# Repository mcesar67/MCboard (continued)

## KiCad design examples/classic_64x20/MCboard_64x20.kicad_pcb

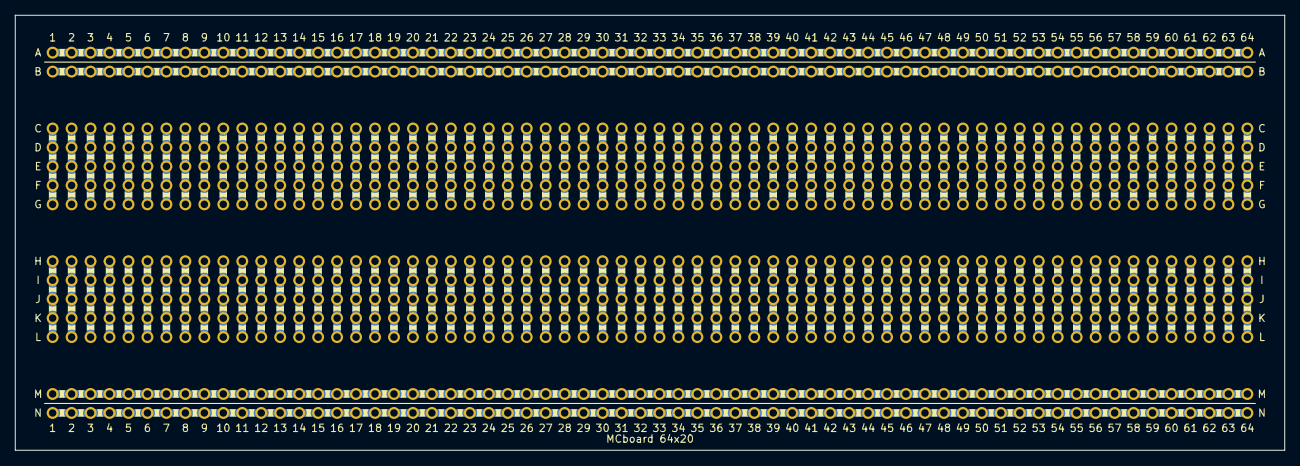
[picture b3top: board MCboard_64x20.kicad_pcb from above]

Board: 2 copper layers, 170.0 x 58.3 mm, 896 parts (0 on the bottom side), 132 nets.

Parts:
PBH1, PBH2, PBH3, PBH4, PBH5, PBH6, PBH7, PBH8, PBH9, PBH10, PBH11, PBH12, PBH13, PBH14, PBH15, PBH16, PBH17, PBH18, PBH19, PBH20, PBH21, PBH22, PBH23, PBH24, PBH25, PBH26, PBH27, PBH28, PBH29, PBH30, PBH31, PBH32, PBH33, PBH34, PBH35, PBH36, PBH37, PBH38, PBH39, PBH40, PBH41, PBH42, PBH43, PBH44, PBH45, PBH46, PBH47, PBH48, PBH49, PBH50, PBH51, PBH52, PBH53, PBH54, PBH55, PBH56, PBH57, PBH58, PBH59, PBH60, PBH61, PBH62, PBH63, PBH64, PBH65, PBH66, PBH67, PBH68, PBH69, PBH70, PBH71, PBH72, PBH73, PBH74, PBH75, PBH76, PBH77, PBH78, PBH79, PBH80, PBH81, PBH82, PBH83, PBH84, PBH85, PBH86, PBH87, PBH88, PBH89, PBH90, PBH91, PBH92, PBH93, PBH94, PBH95, PBH96, PBH97, PBH98, PBH99, PBH100, PBH101, PBH102, PBH103, PBH104, PBH105, PBH106, PBH107, PBH108, PBH109, PBH110, PBH111, PBH112, PBH113, PBH114, PBH115, PBH116, PBH117, PBH118, PBH119, PBH120, PBH121, PBH122, PBH123, PBH124, PBH125, PBH126, PBH127, PBH128, PBH129, PBH130, PBH131, PBH132, PBH133, PBH134, PBH135, PBH136, PBH137, PBH138, PBH139, PBH140, PBH141, PBH142, PBH143, PBH144, PBH145, PBH146, PBH147, PBH148, PBH149, PBH150, PBH151, PBH152, PBH153, PBH154, PBH155, PBH156, PBH157, PBH158, PBH159, PBH160, PBH161, PBH162, PBH163, PBH164, PBH165, PBH166, PBH167, PBH168, PBH169, PBH170, PBH171, PBH172, PBH173, PBH174, PBH175, PBH176, PBH177, PBH178, PBH179, PBH180, PBH181, PBH182, PBH183, PBH184, PBH185, PBH186, PBH187, PBH188, PBH189, PBH190, PBH191, PBH192, PBH193, PBH194, PBH195, PBH196, PBH197, PBH198, PBH199, PBH200, PBH201, PBH202, PBH203, PBH204, PBH205, PBH206, PBH207, PBH208, PBH209, PBH210, PBH211, PBH212, PBH213, PBH214, PBH215, PBH216, PBH217, PBH218, PBH219, PBH220, PBH221, PBH222, PBH223, PBH224, PBH225, PBH226, PBH227, PBH228, PBH229, PBH230, PBH231, PBH232, PBH233, PBH234, PBH235, PBH236, PBH237, PBH238, PBH239, PBH240, PBH241, PBH242, PBH243, PBH244, PBH245, PBH246, PBH247, PBH248, PBH249, PBH250, PBH251, PBH252, PBH253, PBH254, PBH255, PBH256, PBH257, PBH258, PBH259, PBH260, PBH261, PBH262, PBH263, PBH264, PBH265, PBH266, PBH267, PBH268, PBH269, PBH270, PBH271, PBH272, PBH273, PBH274, PBH275, PBH276, PBH277, PBH278, PBH279, PBH280, PBH281, PBH282, PBH283, PBH284, PBH285, PBH286, PBH287, PBH288, PBH289, PBH290, PBH291, PBH292, PBH293, PBH294, PBH295, PBH296, PBH297, PBH298, PBH299, PBH300, PBH301, PBH302, PBH303, PBH304, PBH305, PBH306, PBH307, PBH308, PBH309, PBH310, PBH311, PBH312, PBH313, PBH314, PBH315, PBH316, PBH317, PBH318, PBH319, PBH320, PBH321, PBH322, PBH323, PBH324, PBH325, PBH326, PBH327, PBH328, PBH329, PBH330, PBH331, PBH332, PBH333, PBH334, PBH335, PBH336, PBH337, PBH338, PBH339, PBH340, PBH341, PBH342, PBH343, PBH344, PBH345, PBH346, PBH347, PBH348, PBH349, PBH350, PBH351, PBH352, PBH353, PBH354, PBH355, PBH356, PBH357, PBH358, PBH359, PBH360, PBH361, PBH362, PBH363, PBH364, PBH365, PBH366, PBH367, PBH368, PBH369, PBH370, PBH371, PBH372, PBH373, PBH374, PBH375, PBH376, PBH377, PBH378, PBH379, PBH380, PBH381, PBH382, PBH383, PBH384, PBH385, PBH386, PBH387, PBH388, PBH389, PBH390, PBH391, PBH392, PBH393, PBH394, PBH395, PBH396, PBH397, PBH398, PBH399, PBH400, PBH401, PBH402, PBH403, PBH404, PBH405, PBH406, PBH407, PBH408, PBH409, PBH410, PBH411, PBH412, PBH413, PBH414, PBH415, PBH416, PBH417, PBH418, PBH419, PBH420, PBH421, PBH422, PBH423, PBH424, PBH425, PBH426, PBH427, PBH428, PBH429, PBH430, PBH431, PBH432, PBH433, PBH434, PBH435, PBH436, PBH437, PBH438, PBH439, PBH440, PBH441, PBH442, PBH443, PBH444, PBH445, PBH446, PBH447, PBH448, PBH449, PBH450, PBH451, PBH452, PBH453, PBH454, PBH455, PBH456, PBH457, PBH458, PBH459, PBH460, PBH461, PBH462, PBH463, PBH464, PBH465, PBH466, PBH467, PBH468, PBH469, PBH470, PBH471, PBH472, PBH473, PBH474, PBH475, PBH476, PBH477, PBH478, PBH479, PBH480, PBH481, PBH482, PBH483, PBH484, PBH485, PBH486, PBH487, PBH488, PBH489, PBH490, PBH491, PBH492, PBH493, PBH494, PBH495, PBH496, PBH497, PBH498, PBH499, PBH500, PBH501, PBH502, PBH503, PBH504, PBH505, PBH506, PBH507, PBH508, PBH509, PBH510, PBH511, PBH512, PBH513, PBH514, PBH515, PBH516, PBH517, PBH518, PBH519, PBH520, PBH521, PBH522, PBH523, PBH524, PBH525, PBH526, PBH527, PBH528, PBH529, PBH530, PBH531, PBH532, PBH533, PBH534, PBH535, PBH536, PBH537, PBH538, PBH539, PBH540, PBH541, PBH542, PBH543, PBH544, PBH545, PBH546, PBH547, PBH548, PBH549, PBH550, PBH551, PBH552, PBH553, PBH554, PBH555, PBH556, PBH557, PBH558, PBH559, PBH560, PBH561, PBH562, PBH563, PBH564, PBH565, PBH566, PBH567, PBH568, PBH569, PBH570, PBH571, PBH572, PBH573, PBH574, PBH575, PBH576, PBH577, PBH578, PBH579, PBH580, PBH581, PBH582, PBH583, PBH584, PBH585, PBH586, PBH587, PBH588, PBH589, PBH590, PBH591, PBH592, PBH593, PBH594, PBH595, PBH596, PBH597, PBH598, PBH599, PBH600, PBH601, PBH602, PBH603, PBH604, PBH605, PBH606, PBH607, PBH608, PBH609, PBH610, PBH611, PBH612, PBH613, PBH614, PBH615, PBH616, PBH617, PBH618, PBH619, PBH620, PBH621, PBH622, PBH623, PBH624, PBH625, PBH626, PBH627, PBH628, PBH629, PBH630, PBH631, PBH632, PBH633, PBH634, PBH635, PBH636, PBH637, PBH638, PBH639, PBH640, PBH641, PBH642, PBH643, PBH644, PBH645, PBH646, PBH647, PBH648, PBH649, PBH650, PBH651, PBH652, PBH653, PBH654, PBH655, PBH656, PBH657, PBH658, PBH659, PBH660, PBH661, PBH662, PBH663, PBH664, PBH665, PBH666, PBH667, PBH668, PBH669, PBH670, PBH671, PBH672, PBH673, PBH674, PBH675, PBH676, PBH677, PBH678, PBH679, PBH680, PBH681, PBH682, PBH683, PBH684, PBH685, PBH686, PBH687, PBH688, PBH689, PBH690, PBH691, PBH692, PBH693, PBH694, PBH695, PBH696, PBH697, PBH698, PBH699, PBH700, PBH701, PBH702, PBH703, PBH704, PBH705, PBH706, PBH707, PBH708, PBH709, PBH710, PBH711, PBH712, PBH713, PBH714, PBH715, PBH716, PBH717, PBH718, PBH719, PBH720, PBH721, PBH722, PBH723, PBH724, PBH725, PBH726, PBH727, PBH728, PBH729, PBH730, PBH731, PBH732, PBH733, PBH734, PBH735, PBH736, PBH737, PBH738, PBH739, PBH740, PBH741, PBH742, PBH743, PBH744, PBH745, PBH746, PBH747, PBH748, PBH749, PBH750, PBH751, PBH752, PBH753, PBH754, PBH755, PBH756, PBH757, PBH758, PBH759, PBH760, PBH761, PBH762, PBH763, PBH764, PBH765, PBH766, PBH767, PBH768, PBH769, PBH770, PBH771, PBH772, PBH773, PBH774, PBH775, PBH776, PBH777, PBH778, PBH779, PBH780, PBH781, PBH782, PBH783, PBH784, PBH785, PBH786, PBH787, PBH788, PBH789, PBH790, PBH791, PBH792, PBH793, PBH794, PBH795, PBH796, PBH797, PBH798, PBH799, PBH800, PBH801, PBH802, PBH803, PBH804, PBH805, PBH806, PBH807, PBH808, PBH809, PBH810, PBH811, PBH812, PBH813, PBH814, PBH815, PBH816, PBH817, PBH818, PBH819, PBH820, PBH821, PBH822, PBH823, PBH824, PBH825, PBH826, PBH827, PBH828, PBH829, PBH830, PBH831, PBH832, PBH833, PBH834, PBH835, PBH836, PBH837, PBH838, PBH839, PBH840, PBH841, PBH842, PBH843, PBH844, PBH845, PBH846, PBH847, PBH848, PBH849, PBH850, PBH851, PBH852, PBH853, PBH854, PBH855, PBH856, PBH857, PBH858, PBH859, PBH860, PBH861, PBH862, PBH863, PBH864, PBH865, PBH866, PBH867, PBH868, PBH869, PBH870, PBH871, PBH872, PBH873, PBH874, PBH875, PBH876, PBH877, PBH878, PBH879, PBH880, PBH881, PBH882, PBH883, PBH884, PBH885, PBH886, PBH887, PBH888, PBH889, PBH890, PBH891, PBH892, PBH893, PBH894, PBH895, PBH896: hole; Hole

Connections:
BUS_R1: PBH1.1, PBH15.1, PBH29.1, PBH43.1, PBH57.1, PBH71.1, PBH85.1, PBH99.1, PBH113.1, PBH127.1, PBH141.1, PBH155.1, PBH169.1, PBH183.1, PBH197.1, PBH211.1, PBH225.1, PBH239.1, PBH253.1, PBH267.1, PBH281.1, PBH295.1, PBH309.1, PBH323.1, PBH337.1, PBH351.1, PBH365.1, PBH379.1, PBH393.1, PBH407.1, PBH421.1, PBH435.1, PBH449.1, PBH463.1, PBH477.1, PBH491.1, PBH505.1, PBH519.1, PBH533.1, PBH547.1, PBH561.1, PBH575.1, PBH589.1, PBH603.1, PBH617.1, PBH631.1, PBH645.1, PBH659.1, PBH673.1, PBH687.1, PBH701.1, PBH715.1, PBH729.1, PBH743.1, PBH757.1, PBH771.1, PBH785.1, PBH799.1, PBH813.1, PBH827.1, PBH841.1, PBH855.1, PBH869.1, PBH883.1
BUS_R2: PBH2.1, PBH16.1, PBH30.1, PBH44.1, PBH58.1, PBH72.1, PBH86.1, PBH100.1, PBH114.1, PBH128.1, PBH142.1, PBH156.1, PBH170.1, PBH184.1, PBH198.1, PBH212.1, PBH226.1, PBH240.1, PBH254.1, PBH268.1, PBH282.1, PBH296.1, PBH310.1, PBH324.1, PBH338.1, PBH352.1, PBH366.1, PBH380.1, PBH394.1, PBH408.1, PBH422.1, PBH436.1, PBH450.1, PBH464.1, PBH478.1, PBH492.1, PBH506.1, PBH520.1, PBH534.1, PBH548.1, PBH562.1, PBH576.1, PBH590.1, PBH604.1, PBH618.1, PBH632.1, PBH646.1, PBH660.1, PBH674.1, PBH688.1, PBH702.1, PBH716.1, PBH730.1, PBH744.1, PBH758.1, PBH772.1, PBH786.1, PBH800.1, PBH814.1, PBH828.1, PBH842.1, PBH856.1, PBH870.1, PBH884.1
BUS_R13: PBH13.1, PBH27.1, PBH41.1, PBH55.1, PBH69.1, PBH83.1, PBH97.1, PBH111.1, PBH125.1, PBH139.1, PBH153.1, PBH167.1, PBH181.1, PBH195.1, PBH209.1, PBH223.1, PBH237.1, PBH251.1, PBH265.1, PBH279.1, PBH293.1, PBH307.1, PBH321.1, PBH335.1, PBH349.1, PBH363.1, PBH377.1, PBH391.1, PBH405.1, PBH419.1, PBH433.1, PBH447.1, PBH461.1, PBH475.1, PBH489.1, PBH503.1, PBH517.1, PBH531.1, PBH545.1, PBH559.1, PBH573.1, PBH587.1, PBH601.1, PBH615.1, PBH629.1, PBH643.1, PBH657.1, PBH671.1, PBH685.1, PBH699.1, PBH713.1, PBH727.1, PBH741.1, PBH755.1, PBH769.1, PBH783.1, PBH797.1, PBH811.1, PBH825.1, PBH839.1, PBH853.1, PBH867.1, PBH881.1, PBH895.1
BUS_R14: PBH14.1, PBH28.1, PBH42.1, PBH56.1, PBH70.1, PBH84.1, PBH98.1, PBH112.1, PBH126.1, PBH140.1, PBH154.1, PBH168.1, PBH182.1, PBH196.1, PBH210.1, PBH224.1, PBH238.1, PBH252.1, PBH266.1, PBH280.1, PBH294.1, PBH308.1, PBH322.1, PBH336.1, PBH350.1, PBH364.1, PBH378.1, PBH392.1, PBH406.1, PBH420.1, PBH434.1, PBH448.1, PBH462.1, PBH476.1, PBH490.1, PBH504.1, PBH518.1, PBH532.1, PBH546.1, PBH560.1, PBH574.1, PBH588.1, PBH602.1, PBH616.1, PBH630.1, PBH644.1, PBH658.1, PBH672.1, PBH686.1, PBH700.1, PBH714.1, PBH728.1, PBH742.1, PBH756.1, PBH770.1, PBH784.1, PBH798.1, PBH812.1, PBH826.1, PBH840.1, PBH854.1, PBH868.1, PBH882.1, PBH896.1
C1_R3: PBH3.1, PBH4.1, PBH5.1, PBH6.1, PBH7.1
C1_R8: PBH8.1, PBH9.1, PBH10.1, PBH11.1, PBH12.1
C2_R3: PBH17.1, PBH18.1, PBH19.1, PBH20.1, PBH21.1
C2_R8: PBH22.1, PBH23.1, PBH24.1, PBH25.1, PBH26.1
C3_R3: PBH31.1, PBH32.1, PBH33.1, PBH34.1, PBH35.1
C3_R8: PBH36.1, PBH37.1, PBH38.1, PBH39.1, PBH40.1
C4_R3: PBH45.1, PBH46.1, PBH47.1, PBH48.1, PBH49.1
C4_R8: PBH50.1, PBH51.1, PBH52.1, PBH53.1, PBH54.1
C5_R3: PBH59.1, PBH60.1, PBH61.1, PBH62.1, PBH63.1
C5_R8: PBH64.1, PBH65.1, PBH66.1, PBH67.1, PBH68.1
C6_R3: PBH73.1, PBH74.1, PBH75.1, PBH76.1, PBH77.1
C6_R8: PBH78.1, PBH79.1, PBH80.1, PBH81.1, PBH82.1
C7_R3: PBH87.1, PBH88.1, PBH89.1, PBH90.1, PBH91.1
C7_R8: PBH92.1, PBH93.1, PBH94.1, PBH95.1, PBH96.1
C8_R3: PBH101.1, PBH102.1, PBH103.1, PBH104.1, PBH105.1
C8_R8: PBH106.1, PBH107.1, PBH108.1, PBH109.1, PBH110.1
C9_R3: PBH115.1, PBH116.1, PBH117.1, PBH118.1, PBH119.1
C9_R8: PBH120.1, PBH121.1, PBH122.1, PBH123.1, PBH124.1
C10_R3: PBH129.1, PBH130.1, PBH131.1, PBH132.1, PBH133.1
C10_R8: PBH134.1, PBH135.1, PBH136.1, PBH137.1, PBH138.1
C11_R3: PBH143.1, PBH144.1, PBH145.1, PBH146.1, PBH147.1
C11_R8: PBH148.1, PBH149.1, PBH150.1, PBH151.1, PBH152.1
C12_R3: PBH157.1, PBH158.1, PBH159.1, PBH160.1, PBH161.1
C12_R8: PBH162.1, PBH163.1, PBH164.1, PBH165.1, PBH166.1
C13_R3: PBH171.1, PBH172.1, PBH173.1, PBH174.1, PBH175.1
C13_R8: PBH176.1, PBH177.1, PBH178.1, PBH179.1, PBH180.1
C14_R3: PBH185.1, PBH186.1, PBH187.1, PBH188.1, PBH189.1
C14_R8: PBH190.1, PBH191.1, PBH192.1, PBH193.1, PBH194.1
C15_R3: PBH199.1, PBH200.1, PBH201.1, PBH202.1, PBH203.1
C15_R8: PBH204.1, PBH205.1, PBH206.1, PBH207.1, PBH208.1
C16_R3: PBH213.1, PBH214.1, PBH215.1, PBH216.1, PBH217.1
C16_R8: PBH218.1, PBH219.1, PBH220.1, PBH221.1, PBH222.1
C17_R3: PBH227.1, PBH228.1, PBH229.1, PBH230.1, PBH231.1
C17_R8: PBH232.1, PBH233.1, PBH234.1, PBH235.1, PBH236.1
C18_R3: PBH241.1, PBH242.1, PBH243.1, PBH244.1, PBH245.1
C18_R8: PBH246.1, PBH247.1, PBH248.1, PBH249.1, PBH250.1
C19_R3: PBH255.1, PBH256.1, PBH257.1, PBH258.1, PBH259.1
C19_R8: PBH260.1, PBH261.1, PBH262.1, PBH263.1, PBH264.1
C20_R3: PBH269.1, PBH270.1, PBH271.1, PBH272.1, PBH273.1
C20_R8: PBH274.1, PBH275.1, PBH276.1, PBH277.1, PBH278.1
C21_R3: PBH283.1, PBH284.1, PBH285.1, PBH286.1, PBH287.1
C21_R8: PBH288.1, PBH289.1, PBH290.1, PBH291.1, PBH292.1
C22_R3: PBH297.1, PBH298.1, PBH299.1, PBH300.1, PBH301.1
C22_R8: PBH302.1, PBH303.1, PBH304.1, PBH305.1, PBH306.1
C23_R3: PBH311.1, PBH312.1, PBH313.1, PBH314.1, PBH315.1
C23_R8: PBH316.1, PBH317.1, PBH318.1, PBH319.1, PBH320.1
C24_R3: PBH325.1, PBH326.1, PBH327.1, PBH328.1, PBH329.1
C24_R8: PBH330.1, PBH331.1, PBH332.1, PBH333.1, PBH334.1
C25_R3: PBH339.1, PBH340.1, PBH341.1, PBH342.1, PBH343.1
C25_R8: PBH344.1, PBH345.1, PBH346.1, PBH347.1, PBH348.1
C26_R3: PBH353.1, PBH354.1, PBH355.1, PBH356.1, PBH357.1
C26_R8: PBH358.1, PBH359.1, PBH360.1, PBH361.1, PBH362.1
C27_R3: PBH367.1, PBH368.1, PBH369.1, PBH370.1, PBH371.1
C27_R8: PBH372.1, PBH373.1, PBH374.1, PBH375.1, PBH376.1
C28_R3: PBH381.1, PBH382.1, PBH383.1, PBH384.1, PBH385.1
C28_R8: PBH386.1, PBH387.1, PBH388.1, PBH389.1, PBH390.1
C29_R3: PBH395.1, PBH396.1, PBH397.1, PBH398.1, PBH399.1
C29_R8: PBH400.1, PBH401.1, PBH402.1, PBH403.1, PBH404.1
C30_R3: PBH409.1, PBH410.1, PBH411.1, PBH412.1, PBH413.1
C30_R8: PBH414.1, PBH415.1, PBH416.1, PBH417.1, PBH418.1
C31_R3: PBH423.1, PBH424.1, PBH425.1, PBH426.1, PBH427.1
C31_R8: PBH428.1, PBH429.1, PBH430.1, PBH431.1, PBH432.1
C32_R3: PBH437.1, PBH438.1, PBH439.1, PBH440.1, PBH441.1
C32_R8: PBH442.1, PBH443.1, PBH444.1, PBH445.1, PBH446.1
C33_R3: PBH451.1, PBH452.1, PBH453.1, PBH454.1, PBH455.1
C33_R8: PBH456.1, PBH457.1, PBH458.1, PBH459.1, PBH460.1
C34_R3: PBH465.1, PBH466.1, PBH467.1, PBH468.1, PBH469.1
C34_R8: PBH470.1, PBH471.1, PBH472.1, PBH473.1, PBH474.1
C35_R3: PBH479.1, PBH480.1, PBH481.1, PBH482.1, PBH483.1
C35_R8: PBH484.1, PBH485.1, PBH486.1, PBH487.1, PBH488.1
C36_R3: PBH493.1, PBH494.1, PBH495.1, PBH496.1, PBH497.1
C36_R8: PBH498.1, PBH499.1, PBH500.1, PBH501.1, PBH502.1
C37_R3: PBH507.1, PBH508.1, PBH509.1, PBH510.1, PBH511.1
C37_R8: PBH512.1, PBH513.1, PBH514.1, PBH515.1, PBH516.1
C38_R3: PBH521.1, PBH522.1, PBH523.1, PBH524.1, PBH525.1
C38_R8: PBH526.1, PBH527.1, PBH528.1, PBH529.1, PBH530.1
C39_R3: PBH535.1, PBH536.1, PBH537.1, PBH538.1, PBH539.1
C39_R8: PBH540.1, PBH541.1, PBH542.1, PBH543.1, PBH544.1
C40_R3: PBH549.1, PBH550.1, PBH551.1, PBH552.1, PBH553.1
C40_R8: PBH554.1, PBH555.1, PBH556.1, PBH557.1, PBH558.1
C41_R3: PBH563.1, PBH564.1, PBH565.1, PBH566.1, PBH567.1
C41_R8: PBH568.1, PBH569.1, PBH570.1, PBH571.1, PBH572.1
C42_R3: PBH577.1, PBH578.1, PBH579.1, PBH580.1, PBH581.1
C42_R8: PBH582.1, PBH583.1, PBH584.1, PBH585.1, PBH586.1
C43_R3: PBH591.1, PBH592.1, PBH593.1, PBH594.1, PBH595.1
C43_R8: PBH596.1, PBH597.1, PBH598.1, PBH599.1, PBH600.1
C44_R3: PBH605.1, PBH606.1, PBH607.1, PBH608.1, PBH609.1
C44_R8: PBH610.1, PBH611.1, PBH612.1, PBH613.1, PBH614.1
C45_R3: PBH619.1, PBH620.1, PBH621.1, PBH622.1, PBH623.1
C45_R8: PBH624.1, PBH625.1, PBH626.1, PBH627.1, PBH628.1
C46_R3: PBH633.1, PBH634.1, PBH635.1, PBH636.1, PBH637.1
C46_R8: PBH638.1, PBH639.1, PBH640.1, PBH641.1, PBH642.1
C47_R3: PBH647.1, PBH648.1, PBH649.1, PBH650.1, PBH651.1
C47_R8: PBH652.1, PBH653.1, PBH654.1, PBH655.1, PBH656.1
C48_R3: PBH661.1, PBH662.1, PBH663.1, PBH664.1, PBH665.1
C48_R8: PBH666.1, PBH667.1, PBH668.1, PBH669.1, PBH670.1
C49_R3: PBH675.1, PBH676.1, PBH677.1, PBH678.1, PBH679.1
C49_R8: PBH680.1, PBH681.1, PBH682.1, PBH683.1, PBH684.1
C50_R3: PBH689.1, PBH690.1, PBH691.1, PBH692.1, PBH693.1
C50_R8: PBH694.1, PBH695.1, PBH696.1, PBH697.1, PBH698.1
C51_R3: PBH703.1, PBH704.1, PBH705.1, PBH706.1, PBH707.1
C51_R8: PBH708.1, PBH709.1, PBH710.1, PBH711.1, PBH712.1
C52_R3: PBH717.1, PBH718.1, PBH719.1, PBH720.1, PBH721.1
C52_R8: PBH722.1, PBH723.1, PBH724.1, PBH725.1, PBH726.1
C53_R3: PBH731.1, PBH732.1, PBH733.1, PBH734.1, PBH735.1
C53_R8: PBH736.1, PBH737.1, PBH738.1, PBH739.1, PBH740.1
C54_R3: PBH745.1, PBH746.1, PBH747.1, PBH748.1, PBH749.1
C54_R8: PBH750.1, PBH751.1, PBH752.1, PBH753.1, PBH754.1
C55_R3: PBH759.1, PBH760.1, PBH761.1, PBH762.1, PBH763.1
C55_R8: PBH764.1, PBH765.1, PBH766.1, PBH767.1, PBH768.1
C56_R3: PBH773.1, PBH774.1, PBH775.1, PBH776.1, PBH777.1
C56_R8: PBH778.1, PBH779.1, PBH780.1, PBH781.1, PBH782.1
C57_R3: PBH787.1, PBH788.1, PBH789.1, PBH790.1, PBH791.1
C57_R8: PBH792.1, PBH793.1, PBH794.1, PBH795.1, PBH796.1
C58_R3: PBH801.1, PBH802.1, PBH803.1, PBH804.1, PBH805.1
C58_R8: PBH806.1, PBH807.1, PBH808.1, PBH809.1, PBH810.1
C59_R3: PBH815.1, PBH816.1, PBH817.1, PBH818.1, PBH819.1
C59_R8: PBH820.1, PBH821.1, PBH822.1, PBH823.1, PBH824.1
C60_R3: PBH829.1, PBH830.1, PBH831.1, PBH832.1, PBH833.1
C60_R8: PBH834.1, PBH835.1, PBH836.1, PBH837.1, PBH838.1
C61_R3: PBH843.1, PBH844.1, PBH845.1, PBH846.1, PBH847.1
C61_R8: PBH848.1, PBH849.1, PBH850.1, PBH851.1, PBH852.1
C62_R3: PBH857.1, PBH858.1, PBH859.1, PBH860.1, PBH861.1
C62_R8: PBH862.1, PBH863.1, PBH864.1, PBH865.1, PBH866.1
C63_R3: PBH871.1, PBH872.1, PBH873.1, PBH874.1, PBH875.1
C63_R8: PBH876.1, PBH877.1, PBH878.1, PBH879.1, PBH880.1
C64_R3: PBH885.1, PBH886.1, PBH887.1, PBH888.1, PBH889.1
C64_R8: PBH890.1, PBH891.1, PBH892.1, PBH893.1, PBH894.1

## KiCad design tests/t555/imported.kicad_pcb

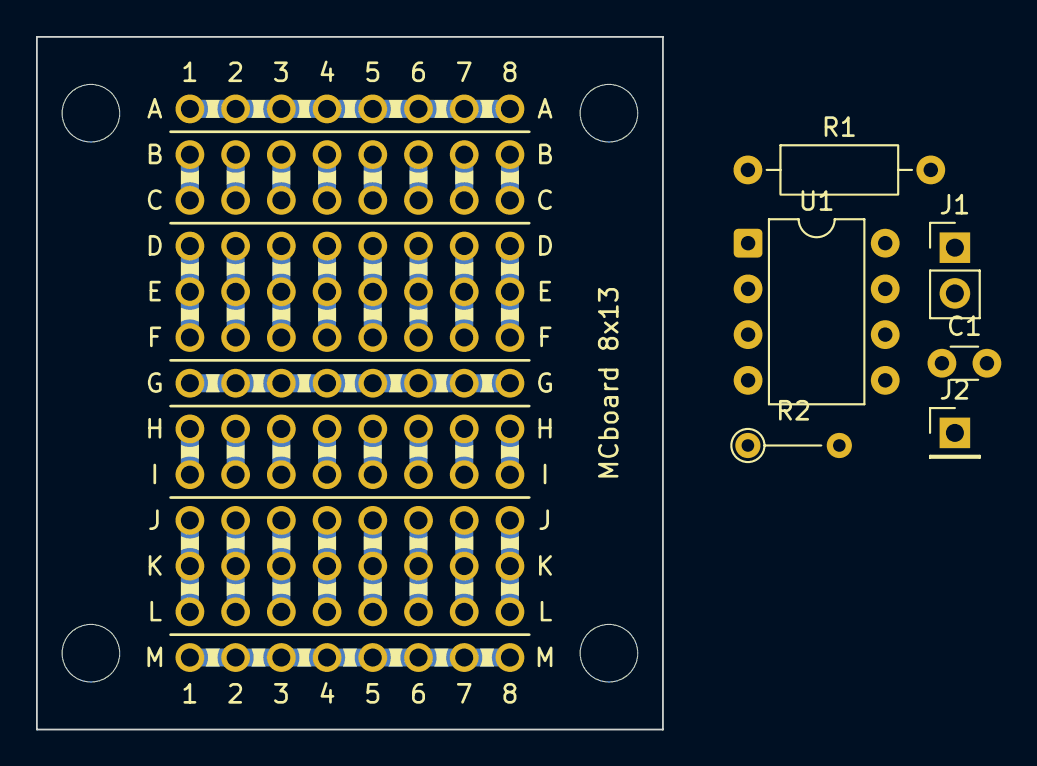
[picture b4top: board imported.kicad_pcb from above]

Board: 2 copper layers, 34.8 x 38.5 mm, 162 parts (0 on the bottom side), 40 nets.

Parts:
C1: 100n; C_Disc_D3.0mm_W1.6mm_P2.50mm
H1, H2, H3, H4, H5, H6, H7, H8, H9, H10, H11, H12, H13, H14, H15, H16, H17, H18, H19, H20, H21, H22, H23, H24, H25, H26, H27, H28, H29, H30, H31, H32, H33, H34, H35, H36, H37, H38, H39, H40, H41, H42, H43, H44, H45, H46, H47, H48, H49, H50, H51, H52, H53, H54, H55, H56, H57, H58, H59, H60, H61, H62, H63, H64, H65, H66, H67, H68, H69, H70, H71, H72, H73, H74, H75, H76, H77, H78, H79, H80, H81, H82, H83, H84, H85, H86, H87, H88, H89, H90, H91, H92, H93, H94, H95, H96, H97, H98, H99, H100, H101, H102, H103, H104: hole; Hole
J1: PWR; PinHeader_1x02_P2.54mm_Vertical
J2: OUT; PinHeader_1x01_P2.54mm_Vertical
JP1, JP2, JP3, JP4, JP5, JP6, JP7, JP8, JP9, JP10, JP11, JP12, JP13, JP14, JP15, JP16, JP17, JP18, JP19, JP20, JP21, JP22, JP23, JP24, JP25, JP26, JP27, JP28, JP29, JP30, JP31, JP32, JP33, JP34, JP35, JP36, JP37, JP38, JP39, JP40, JP41, JP42, JP43, JP44, JP45, JP46, JP47, JP48: chevron; ChevronJumper
MH1, MH2, MH3, MH4: mounting hole; MountingHole
R1: 10k; R_Axial_DIN0207_L6.3mm_D2.5mm_P10.16mm_Horizontal
R2: 47k; R_Axial_DIN0204_L3.6mm_D1.6mm_P5.08mm_Vertical
U1: NE555; DIP-8_W7.62mm

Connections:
BUS_R1: H1.1, H14.1, H27.1, H40.1, H53.1, H66.1, H79.1, H92.1, JP1.1, JP7.1, JP13.1, JP19.1, JP25.1, JP31.1, JP37.1, JP43.1
BUS_R7: H7.1, H20.1, H33.1, H46.1, H59.1, H72.1, H85.1, H98.1, JP3.2, JP4.1, JP9.2, JP10.1, JP15.2, JP16.1, JP21.2, JP22.1, JP27.2, JP28.1, JP33.2, JP34.1, JP39.2, JP40.1, JP45.2, JP46.1
BUS_R13: H13.1, H26.1, H39.1, H52.1, H65.1, H78.1, H91.1, H104.1, JP6.2, JP12.2, JP18.2, JP24.2, JP30.2, JP36.2, JP42.2, JP48.2
C1_R2: H2.1, H3.1, JP1.2, JP2.1
C1_R4: H4.1, H5.1, H6.1, JP2.2, JP3.1
C1_R8: H8.1, H9.1, JP4.2, JP5.1
C1_R10: H10.1, H11.1, H12.1, JP5.2, JP6.1
C2_R2: H15.1, H16.1, JP7.2, JP8.1
C2_R4: H17.1, H18.1, H19.1, JP8.2, JP9.1
C2_R8: H21.1, H22.1, JP10.2, JP11.1
C2_R10: H23.1, H24.1, H25.1, JP11.2, JP12.1
C3_R2: H28.1, H29.1, JP13.2, JP14.1
C3_R4: H30.1, H31.1, H32.1, JP14.2, JP15.1
C3_R8: H34.1, H35.1, JP16.2, JP17.1
C3_R10: H36.1, H37.1, H38.1, JP17.2, JP18.1
C4_R2: H41.1, H42.1, JP19.2, JP20.1
C4_R4: H43.1, H44.1, H45.1, JP20.2, JP21.1
C4_R8: H47.1, H48.1, JP22.2, JP23.1
C4_R10: H49.1, H50.1, H51.1, JP23.2, JP24.1
C5_R2: H54.1, H55.1, JP25.2, JP26.1
C5_R4: H56.1, H57.1, H58.1, JP26.2, JP27.1
C5_R8: H60.1, H61.1, JP28.2, JP29.1
C5_R10: H62.1, H63.1, H64.1, JP29.2, JP30.1
C6_R2: H67.1, H68.1, JP31.2, JP32.1
C6_R4: H69.1, H70.1, H71.1, JP32.2, JP33.1
C6_R8: H73.1, H74.1, JP34.2, JP35.1
C6_R10: H75.1, H76.1, H77.1, JP35.2, JP36.1
C7_R2: H80.1, H81.1, JP37.2, JP38.1
C7_R4: H82.1, H83.1, H84.1, JP38.2, JP39.1
C7_R8: H86.1, H87.1, JP40.2, JP41.1
C7_R10: H88.1, H89.1, H90.1, JP41.2, JP42.1
C8_R2: H93.1, H94.1, JP43.2, JP44.1
C8_R4: H95.1, H96.1, H97.1, JP44.2, JP45.1
C8_R8: H99.1, H100.1, JP46.2, JP47.1
C8_R10: H101.1, H102.1, H103.1, JP47.2, JP48.1
DIS: R1.1, R2.2, U1.7
GND: C1.2, J1.2, U1.1
OUT: J2.1, U1.3
TRIG: C1.1, R2.1, U1.2, U1.6
VCC: J1.1, R1.2, U1.4, U1.8

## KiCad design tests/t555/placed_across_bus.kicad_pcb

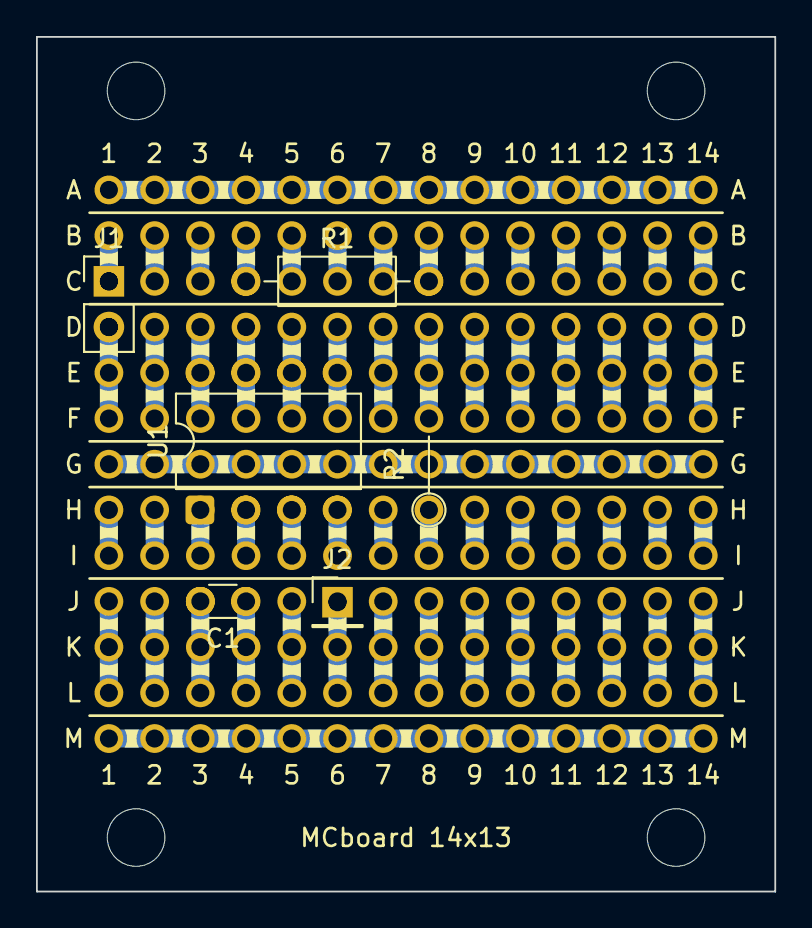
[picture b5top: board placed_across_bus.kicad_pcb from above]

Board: 2 copper layers, 41.0 x 47.5 mm, 276 parts (0 on the bottom side), 64 nets.

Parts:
C1: C_Disc_D3.0mm_W1.6mm_P2.50mm
J1: PinHeader_1x02_P2.54mm_Vertical
J2: PinHeader_1x01_P2.54mm_Vertical
PBH1, PBH2, PBH3, PBH4, PBH5, PBH6, PBH7, PBH8, PBH9, PBH10, PBH11, PBH12, PBH13, PBH14, PBH15, PBH16, PBH17, PBH18, PBH19, PBH20, PBH21, PBH22, PBH23, PBH24, PBH25, PBH26, PBH27, PBH28, PBH29, PBH30, PBH31, PBH32, PBH33, PBH34, PBH35, PBH36, PBH37, PBH38, PBH39, PBH40, PBH41, PBH42, PBH43, PBH44, PBH45, PBH46, PBH47, PBH48, PBH49, PBH50, PBH51, PBH52, PBH53, PBH54, PBH55, PBH56, PBH57, PBH58, PBH59, PBH60, PBH61, PBH62, PBH63, PBH64, PBH65, PBH66, PBH67, PBH68, PBH69, PBH70, PBH71, PBH72, PBH73, PBH74, PBH75, PBH76, PBH77, PBH78, PBH79, PBH80, PBH81, PBH82, PBH83, PBH84, PBH85, PBH86, PBH87, PBH88, PBH89, PBH90, PBH91, PBH92, PBH93, PBH94, PBH95, PBH96, PBH97, PBH98, PBH99, PBH100, PBH101, PBH102, PBH103, PBH104, PBH105, PBH106, PBH107, PBH108, PBH109, PBH110, PBH111, PBH112, PBH113, PBH114, PBH115, PBH116, PBH117, PBH118, PBH119, PBH120, PBH121, PBH122, PBH123, PBH124, PBH125, PBH126, PBH127, PBH128, PBH129, PBH130, PBH131, PBH132, PBH133, PBH134, PBH135, PBH136, PBH137, PBH138, PBH139, PBH140, PBH141, PBH142, PBH143, PBH144, PBH145, PBH146, PBH147, PBH148, PBH149, PBH150, PBH151, PBH152, PBH153, PBH154, PBH155, PBH156, PBH157, PBH158, PBH159, PBH160, PBH161, PBH162, PBH163, PBH164, PBH165, PBH166, PBH167, PBH168, PBH169, PBH170, PBH171, PBH172, PBH173, PBH174, PBH175, PBH176, PBH177, PBH178, PBH179, PBH180, PBH181, PBH182: hole; Hole
PBJP1, PBJP2, PBJP3, PBJP4, PBJP5, PBJP6, PBJP7, PBJP8, PBJP9, PBJP10, PBJP11, PBJP12, PBJP13, PBJP14, PBJP15, PBJP16, PBJP17, PBJP18, PBJP19, PBJP20, PBJP21, PBJP22, PBJP23, PBJP24, PBJP25, PBJP26, PBJP27, PBJP28, PBJP29, PBJP30, PBJP31, PBJP32, PBJP33, PBJP34, PBJP35, PBJP36, PBJP37, PBJP38, PBJP39, PBJP40, PBJP41, PBJP42, PBJP43, PBJP44, PBJP45, PBJP46, PBJP47, PBJP48, PBJP49, PBJP50, PBJP51, PBJP52, PBJP53, PBJP54, PBJP55, PBJP56, PBJP57, PBJP58, PBJP59, PBJP60, PBJP61, PBJP62, PBJP63, PBJP64, PBJP65, PBJP66, PBJP67, PBJP68, PBJP69, PBJP70, PBJP71, PBJP72, PBJP73, PBJP74, PBJP75, PBJP76, PBJP77, PBJP78, PBJP79, PBJP80, PBJP81, PBJP82, PBJP83, PBJP84: chevron; ChevronJumper
PBMH1, PBMH2, PBMH3, PBMH4: mounting hole; MountingHole
R1: R_Axial_DIN0207_L6.3mm_D2.5mm_P10.16mm_Horizontal
R2: R_Axial_DIN0204_L3.6mm_D1.6mm_P5.08mm_Vertical
U1: DIP-8_W7.62mm

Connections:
BUS_R1: PBH1.1, PBH14.1, PBH27.1, PBH40.1, PBH53.1, PBH66.1, PBH79.1, PBH92.1, PBH105.1, PBH118.1, PBH131.1, PBH144.1, PBH157.1, PBH170.1, PBJP1.1, PBJP7.1, PBJP13.1, PBJP19.1, PBJP25.1, PBJP31.1, PBJP37.1, PBJP43.1, PBJP49.1, PBJP55.1, PBJP61.1, PBJP67.1, PBJP73.1, PBJP79.1
BUS_R7: PBH7.1, PBH20.1, PBH33.1, PBH46.1, PBH59.1, PBH72.1, PBH85.1, PBH98.1, PBH111.1, PBH124.1, PBH137.1, PBH150.1, PBH163.1, PBH176.1, PBJP3.2, PBJP4.1, PBJP9.2, PBJP10.1, PBJP15.2, PBJP16.1, PBJP21.2, PBJP22.1, PBJP27.2, PBJP28.1, PBJP33.2, PBJP34.1, PBJP39.2, PBJP40.1, PBJP45.2, PBJP46.1, PBJP51.2, PBJP52.1, PBJP57.2, PBJP58.1, PBJP63.2, PBJP64.1, PBJP69.2, PBJP70.1, PBJP75.2, PBJP76.1, PBJP81.2, PBJP82.1
BUS_R13: PBH13.1, PBH26.1, PBH39.1, PBH52.1, PBH65.1, PBH78.1, PBH91.1, PBH104.1, PBH117.1, PBH130.1, PBH143.1, PBH156.1, PBH169.1, PBH182.1, PBJP6.2, PBJP12.2, PBJP18.2, PBJP24.2, PBJP30.2, PBJP36.2, PBJP42.2, PBJP48.2, PBJP54.2, PBJP60.2, PBJP66.2, PBJP72.2, PBJP78.2, PBJP84.2
C1_R2: PBH2.1, PBH3.1, PBJP1.2, PBJP2.1
C1_R4: PBH4.1, PBH5.1, PBH6.1, PBJP2.2, PBJP3.1
C1_R8: PBH8.1, PBH9.1, PBJP4.2, PBJP5.1
C1_R10: PBH10.1, PBH11.1, PBH12.1, PBJP5.2, PBJP6.1
C2_R2: PBH15.1, PBH16.1, PBJP7.2, PBJP8.1
C2_R4: PBH17.1, PBH18.1, PBH19.1, PBJP8.2, PBJP9.1
C2_R8: PBH21.1, PBH22.1, PBJP10.2, PBJP11.1
C2_R10: PBH23.1, PBH24.1, PBH25.1, PBJP11.2, PBJP12.1
C3_R2: PBH28.1, PBH29.1, PBJP13.2, PBJP14.1
C3_R4: PBH30.1, PBH31.1, PBH32.1, PBJP14.2, PBJP15.1
C3_R8: PBH34.1, PBH35.1, PBJP16.2, PBJP17.1
C3_R10: PBH36.1, PBH37.1, PBH38.1, PBJP17.2, PBJP18.1
C4_R2: PBH41.1, PBH42.1, PBJP19.2, PBJP20.1
C4_R4: PBH43.1, PBH44.1, PBH45.1, PBJP20.2, PBJP21.1
C4_R8: PBH47.1, PBH48.1, PBJP22.2, PBJP23.1
C4_R10: PBH49.1, PBH50.1, PBH51.1, PBJP23.2, PBJP24.1
C5_R2: PBH54.1, PBH55.1, PBJP25.2, PBJP26.1
C5_R4: PBH56.1, PBH57.1, PBH58.1, PBJP26.2, PBJP27.1
C5_R8: PBH60.1, PBH61.1, PBJP28.2, PBJP29.1
C5_R10: PBH62.1, PBH63.1, PBH64.1, PBJP29.2, PBJP30.1
C6_R2: PBH67.1, PBH68.1, PBJP31.2, PBJP32.1
C6_R4: PBH69.1, PBH70.1, PBH71.1, PBJP32.2, PBJP33.1
C6_R8: PBH73.1, PBH74.1, PBJP34.2, PBJP35.1
C6_R10: PBH75.1, PBH76.1, PBH77.1, PBJP35.2, PBJP36.1
C7_R2: PBH80.1, PBH81.1, PBJP37.2, PBJP38.1
C7_R4: PBH82.1, PBH83.1, PBH84.1, PBJP38.2, PBJP39.1
C7_R8: PBH86.1, PBH87.1, PBJP40.2, PBJP41.1
C7_R10: PBH88.1, PBH89.1, PBH90.1, PBJP41.2, PBJP42.1
C8_R2: PBH93.1, PBH94.1, PBJP43.2, PBJP44.1
C8_R4: PBH95.1, PBH96.1, PBH97.1, PBJP44.2, PBJP45.1
C8_R8: PBH99.1, PBH100.1, PBJP46.2, PBJP47.1
C8_R10: PBH101.1, PBH102.1, PBH103.1, PBJP47.2, PBJP48.1
C9_R2: PBH106.1, PBH107.1, PBJP49.2, PBJP50.1
C9_R4: PBH108.1, PBH109.1, PBH110.1, PBJP50.2, PBJP51.1
C9_R8: PBH112.1, PBH113.1, PBJP52.2, PBJP53.1
C9_R10: PBH114.1, PBH115.1, PBH116.1, PBJP53.2, PBJP54.1
C10_R2: PBH119.1, PBH120.1, PBJP55.2, PBJP56.1
C10_R4: PBH121.1, PBH122.1, PBH123.1, PBJP56.2, PBJP57.1
C10_R8: PBH125.1, PBH126.1, PBJP58.2, PBJP59.1
C10_R10: PBH127.1, PBH128.1, PBH129.1, PBJP59.2, PBJP60.1
C11_R2: PBH132.1, PBH133.1, PBJP61.2, PBJP62.1
C11_R4: PBH134.1, PBH135.1, PBH136.1, PBJP62.2, PBJP63.1
C11_R8: PBH138.1, PBH139.1, PBJP64.2, PBJP65.1
C11_R10: PBH140.1, PBH141.1, PBH142.1, PBJP65.2, PBJP66.1
C12_R2: PBH145.1, PBH146.1, PBJP67.2, PBJP68.1
C12_R4: PBH147.1, PBH148.1, PBH149.1, PBJP68.2, PBJP69.1
C12_R8: PBH151.1, PBH152.1, PBJP70.2, PBJP71.1
C12_R10: PBH153.1, PBH154.1, PBH155.1, PBJP71.2, PBJP72.1
C13_R2: PBH158.1, PBH159.1, PBJP73.2, PBJP74.1
C13_R4: PBH160.1, PBH161.1, PBH162.1, PBJP74.2, PBJP75.1
C13_R8: PBH164.1, PBH165.1, PBJP76.2, PBJP77.1
C13_R10: PBH166.1, PBH167.1, PBH168.1, PBJP77.2, PBJP78.1
C14_R2: PBH171.1, PBH172.1, PBJP79.2, PBJP80.1
C14_R4: PBH173.1, PBH174.1, PBH175.1, PBJP80.2, PBJP81.1
C14_R8: PBH177.1, PBH178.1, PBJP82.2, PBJP83.1
C14_R10: PBH179.1, PBH180.1, PBH181.1, PBJP83.2, PBJP84.1
DIS: R1.1, R2.2, U1.7
GND: C1.2, J1.2, U1.1
OUT: J2.1, U1.3
TRIG: C1.1, R2.1, U1.2, U1.6
VCC: J1.1, R1.2, U1.4, U1.8
